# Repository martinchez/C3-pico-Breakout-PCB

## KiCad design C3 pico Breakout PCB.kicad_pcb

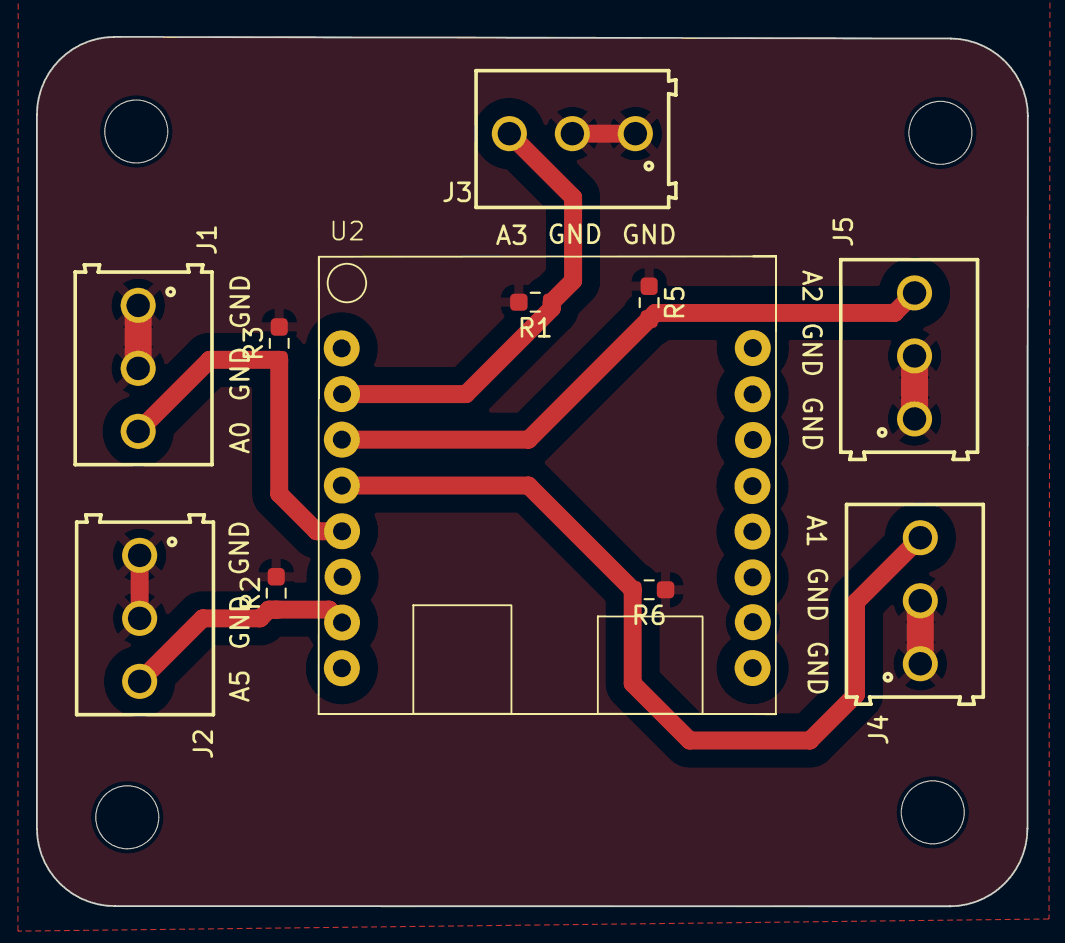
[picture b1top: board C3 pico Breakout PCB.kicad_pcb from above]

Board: 2 copper layers, 55.1 x 48.3 mm, 15 parts (0 on the bottom side), 6 nets.

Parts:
H1, H2, H3, H4: MountingHole; MountingHole_3.5mm
J1, J2, J3, J4, J5: 691214110003
R1, R2, R3, R5, R6: 1MΩ; R_0603_1608Metric_Pad0.98x0.95mm_HandSolder
U2: C3 Pico; c3 pico

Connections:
A0: J1.3, R3.1, U2.0 (A0)
A1: J4.3, R6.2, U2.1 (A1)
A2: J5.3, R5.2, U2.2 (A2)
A3: J3.3, R1.1, U2.3 (A3)
A5: J2.3, R2.1, U2.5 (A5)
GND: J1.1, J1.2, J2.1, J2.2, J3.1, J3.2, J4.1, J4.2, J5.1, J5.2, R1.2, R2.2, R3.2, R5.1, R6.1, U2.GND

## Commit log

2024-11-11 intitial commit
